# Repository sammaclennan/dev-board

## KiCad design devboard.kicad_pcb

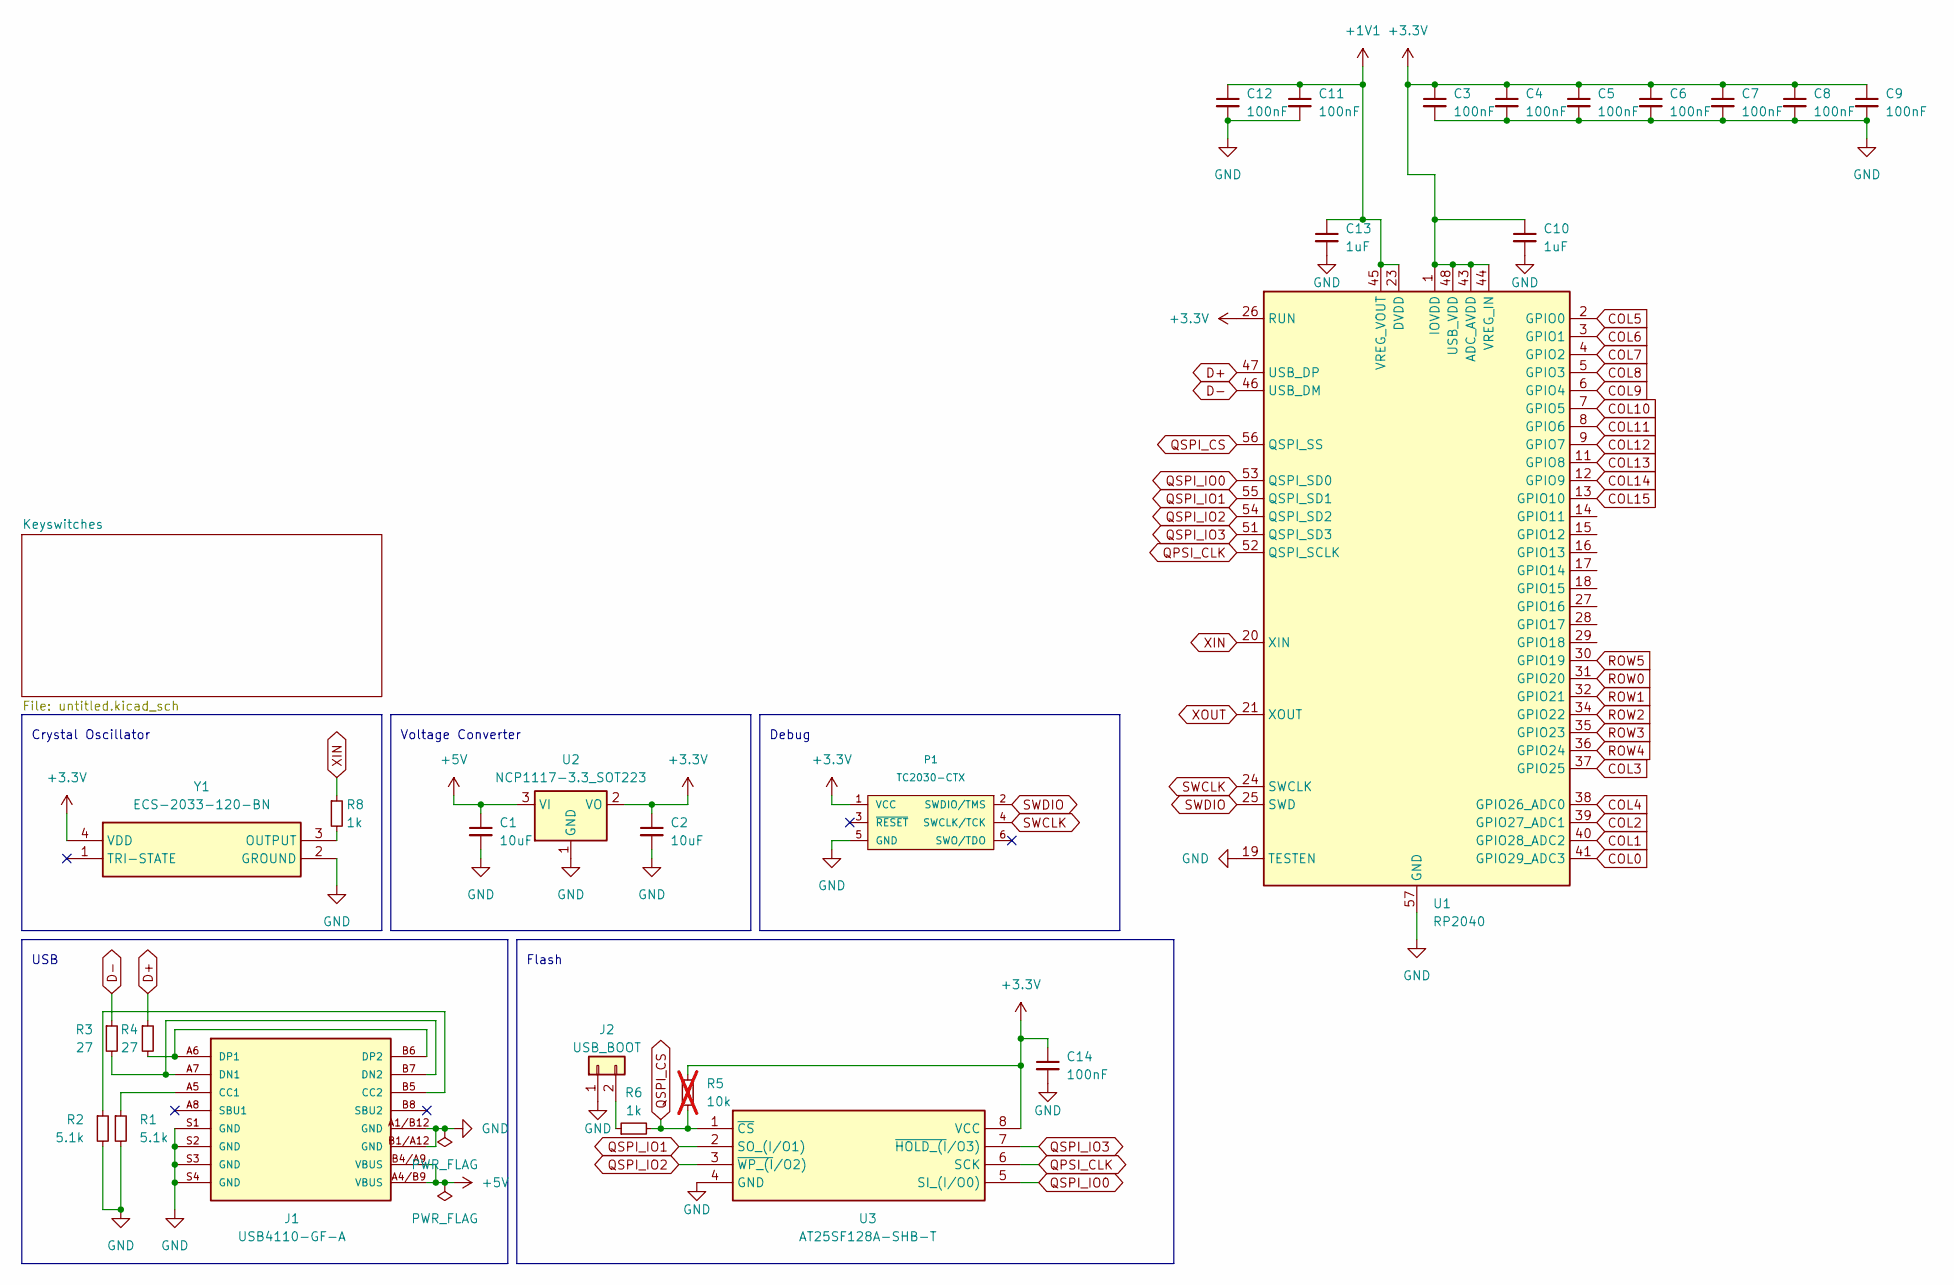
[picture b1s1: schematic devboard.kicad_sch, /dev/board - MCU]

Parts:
C1, C2: 10uF; C_0402_1005Metric
C3, C4, C5, C6, C7, C8, C9, C11, C12, C14: 100nF; C_0402_1005Metric
C10, C13: 1uF; C_0402_1005Metric
J1: USB4110-GF-A; GCT_USB4110GFA
J2: USB_BOOT; PinHeader_1x02_P2.54mm_Vertical
P1: TC2030-CTX; TC2030-IDC-NL
R1, R2: 5.1k; R_0402_1005Metric
R3, R4: 27; R_0402_1005Metric
R5: 10k; R_0402_1005Metric; not fitted
R6, R8: 1k; R_0402_1005Metric
U1: RP2040; QFN-56-1EP_7x7mm_P0.4mm_EP3.2x3.2mm
U2: NCP1117-3.3_SOT223; SOT-223-3_TabPin2
U3: AT25SF128A-SHB-T; Manufacturer_Part_Number AT25SF128A-SHB-T; Mouser Part Number 988-AT25SF128A-SHB-T
Y1: ECS-2033-120-BN; Manufacturer_Part_Number ECS-2033-120-BN; Mouser Part Number 520-2033-120-BN

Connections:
+1V1: C11.1, C12.1, C13.1, U1.23 (DVDD), U1.45 (VREG_VOUT), U1.50 (DVDD)
+3.3V: C2.1, C3.1, C4.1, C5.1, C6.1, C7.1, C8.1, C9.1, C10.1, C14.1, P1.1 (VCC), R5.1, U1.1 (IOVDD), U1.10 (IOVDD), U1.22 (IOVDD), U1.26 (RUN), U1.33 (IOVDD), U1.42 (IOVDD), U1.43 (ADC_AVDD), U1.44 (VREG_IN), U1.48 (USB_VDD), U1.49 (IOVDD), U2.2 (VO), U3.8 (VCC), Y1.4 (VDD)
+5V: C1.1, J1.A4/B9 (VBUS), J1.B4/A9 (VBUS), U2.3 (VI)
COL0: U1.41 (GPIO29_ADC3); also elsewhere on the board
COL1: U1.40 (GPIO28_ADC2); also elsewhere on the board
COL2: U1.39 (GPIO27_ADC1); also elsewhere on the board
COL3: U1.37 (GPIO25); also elsewhere on the board
COL4: U1.38 (GPIO26_ADC0); also elsewhere on the board
COL5: U1.2 (GPIO0); also elsewhere on the board
COL6: U1.3 (GPIO1); also elsewhere on the board
COL7: U1.4 (GPIO2); also elsewhere on the board
COL8: U1.5 (GPIO3); also elsewhere on the board
COL9: U1.6 (GPIO4); also elsewhere on the board
COL10: U1.7 (GPIO5); also elsewhere on the board
COL11: U1.8 (GPIO6); also elsewhere on the board
COL12: U1.9 (GPIO7); also elsewhere on the board
COL13: U1.11 (GPIO8); also elsewhere on the board
COL14: U1.12 (GPIO9); also elsewhere on the board
COL15: U1.13 (GPIO10); also elsewhere on the board
D+: R4.1, U1.47 (USB_DP)
D-: R3.1, U1.46 (USB_DM)
GND: C1.2, C2.2, C3.2, C4.2, C5.2, C6.2, C7.2, C8.2, C9.2, C10.2, C11.2, C12.2, C13.2, C14.2, J1.A1/B12 (GND), J1.B1/A12 (GND), J1.S1 (GND), J1.S2 (GND), J1.S3 (GND), J1.S4 (GND), J2.1, P1.5 (GND), R1.2, R2.2, U1.19 (TESTEN), U1.57 (GND), U2.1 (GND), U3.4 (GND), Y1.2 (GROUND)
unnamed: J1.A5 (CC1), R1.1
unnamed: J1.B5 (CC2), R2.1
unnamed: J1.A7 (DN1), J1.B7 (DN2), R3.2
unnamed: J1.A6 (DP1), J1.B6 (DP2), R4.2
unnamed: J2.2, R6.1
unnamed: R8.2, Y1.3 (OUTPUT)
QPSI_CLK: U1.52 (QSPI_SCLK), U3.6 (SCK)
QSPI_CS: R5.2, R6.2, U1.56 (QSPI_SS), U3.1 (~CS)
QSPI_IO0: U1.53 (QSPI_SD0), U3.5 (SI_(I/O0))
QSPI_IO1: U1.55 (QSPI_SD1), U3.2 (SO_(I/O1))
QSPI_IO2: U1.54 (QSPI_SD2), U3.3 (~WP_(I/O2))
QSPI_IO3: U1.51 (QSPI_SD3), U3.7 (~HOLD_(I/O3))
ROW0: U1.31 (GPIO20); also elsewhere on the board
ROW1: U1.32 (GPIO21); also elsewhere on the board
ROW2: U1.34 (GPIO22); also elsewhere on the board
ROW3: U1.35 (GPIO23); also elsewhere on the board
ROW4: U1.36 (GPIO24); also elsewhere on the board
ROW5: U1.30 (GPIO19); also elsewhere on the board
SWCLK: P1.4 (SWCLK/TCK), U1.24 (SWCLK)
SWDIO: P1.2 (SWDIO/TMS), U1.25 (SWD)
XIN: R8.1, U1.20 (XIN)
XOUT: U1.21 (XOUT)

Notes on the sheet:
Crystal Oscillator
Debug
Voltage Converter
Flash
USB

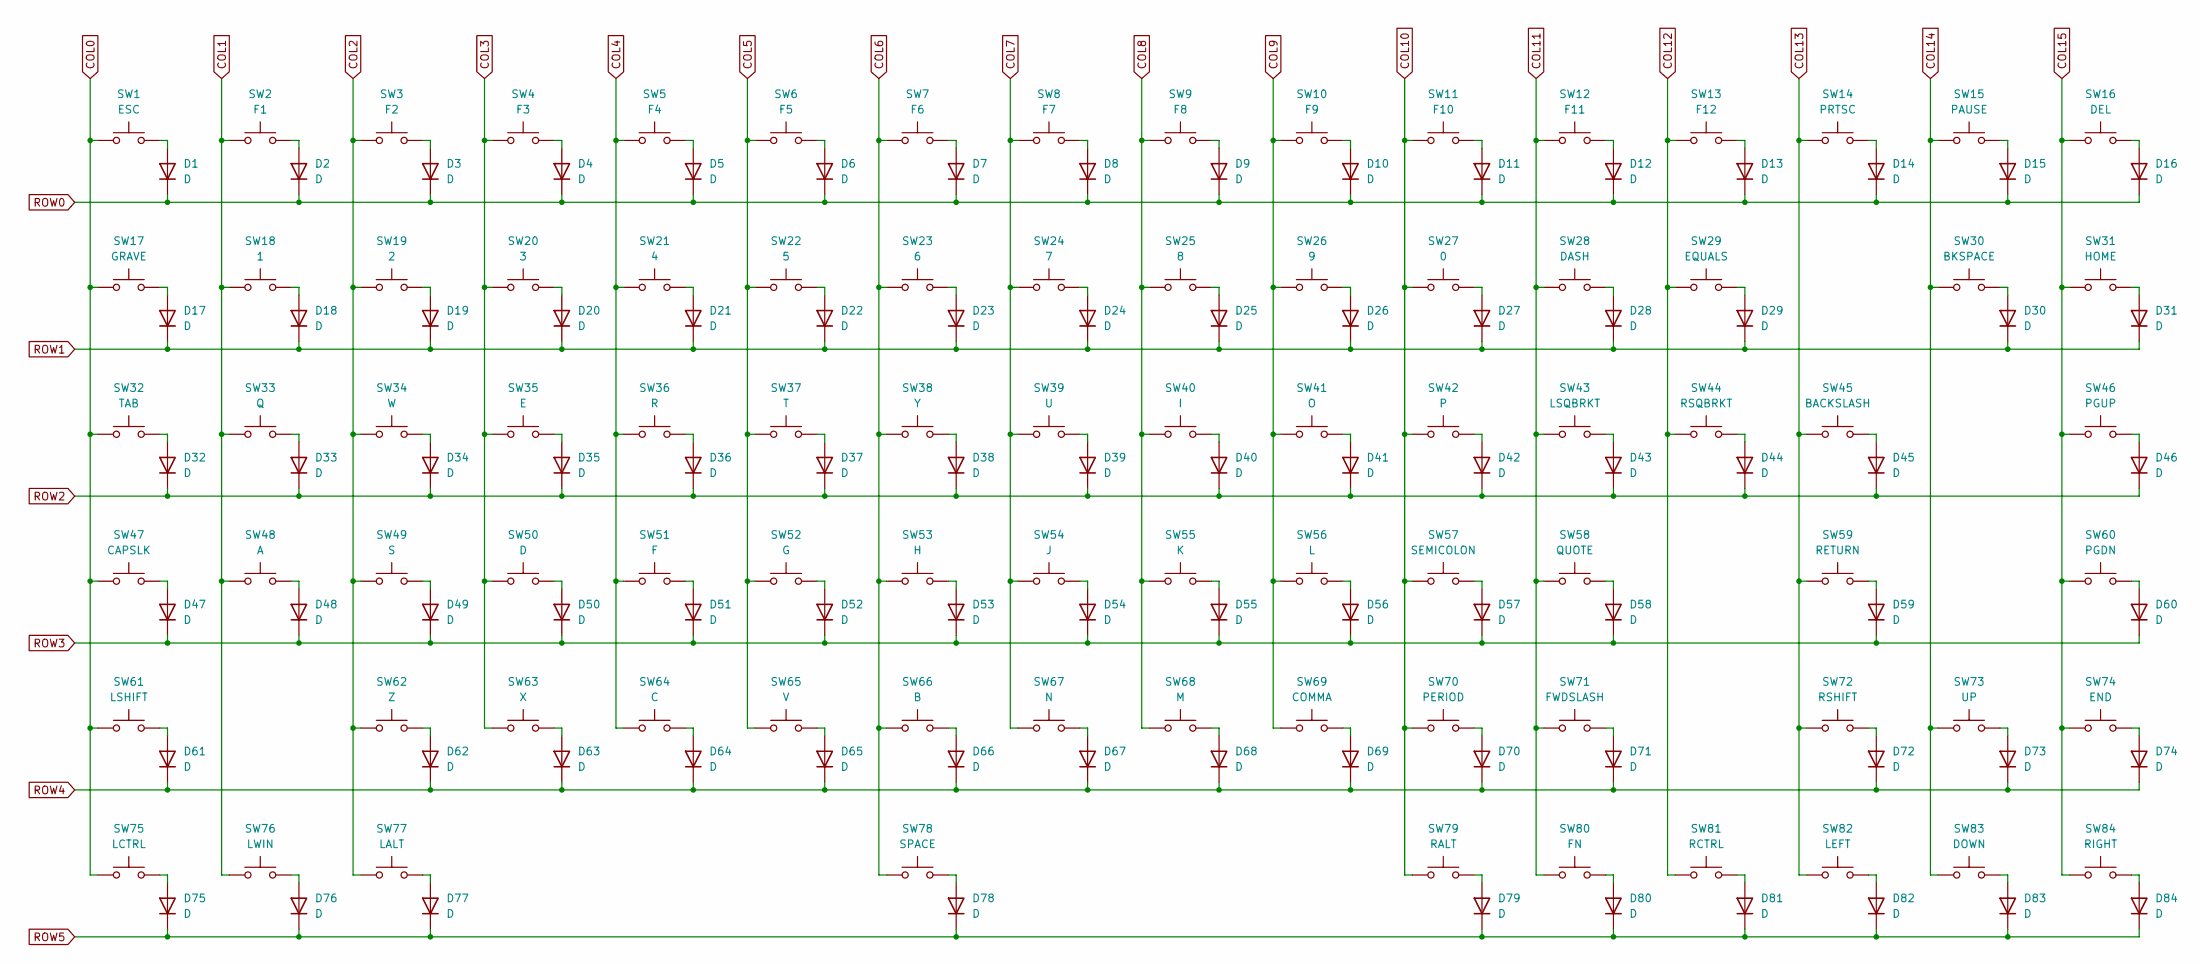
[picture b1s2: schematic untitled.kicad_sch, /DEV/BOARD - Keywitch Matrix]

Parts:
D1, D2, D3, D4, D5, D6, D7, D8, D9, D10, D11, D12, D13, D14, D15, D16, D17, D18, D19, D20, D21, D22, D23, D24, D25, D26, D27, D28, D29, D30, D31, D32, D33, D34, D35, D36, D37, D38, D39, D40, D41, D42, D43, D44, D45, D46, D47, D48, D49, D50, D51, D52, D53, D54, D55, D56, D57, D58, D59, D60, D61, D62, D63, D64, D65, D66, D67, D68, D69, D70, D71, D72, D73, D74, D75, D76, D77, D78, D79, D80, D81, D82, D83, D84: D; D_SOD-323F
SW1: ESC; SW_Cherry_MX_1.00u_PCB
SW2: F1; SW_Cherry_MX_1.00u_PCB
SW3: F2; SW_Cherry_MX_1.00u_PCB
SW4: F3; SW_Cherry_MX_1.00u_PCB
SW5: F4; SW_Cherry_MX_1.00u_PCB
SW6: F5; SW_Cherry_MX_1.00u_PCB
SW7: F6; SW_Cherry_MX_1.00u_PCB
SW8: F7; SW_Cherry_MX_1.00u_PCB
SW9: F8; SW_Cherry_MX_1.00u_PCB
SW10: F9; SW_Cherry_MX_1.00u_PCB
SW11: F10; SW_Cherry_MX_1.00u_PCB
SW12: F11; SW_Cherry_MX_1.00u_PCB
SW13: F12; SW_Cherry_MX_1.00u_PCB
SW14: PRTSC; SW_Cherry_MX_1.00u_PCB
SW15: PAUSE; SW_Cherry_MX_1.00u_PCB
SW16: DEL; SW_Cherry_MX_1.00u_PCB
SW17: GRAVE; SW_Cherry_MX_1.00u_PCB
SW18: 1; SW_Cherry_MX_1.00u_PCB
SW19: 2; SW_Cherry_MX_1.00u_PCB
SW20: 3; SW_Cherry_MX_1.00u_PCB
SW21: 4; SW_Cherry_MX_1.00u_PCB
SW22: 5; SW_Cherry_MX_1.00u_PCB
SW23: 6; SW_Cherry_MX_1.00u_PCB
SW24: 7; SW_Cherry_MX_1.00u_PCB
SW25: 8; SW_Cherry_MX_1.00u_PCB
SW26: 9; SW_Cherry_MX_1.00u_PCB
SW27: 0; SW_Cherry_MX_1.00u_PCB
SW28: DASH; SW_Cherry_MX_1.00u_PCB
SW29: EQUALS; SW_Cherry_MX_1.00u_PCB
SW30: BKSPACE; SW_Cherry_MX_2.00u_PCB
SW31: HOME; SW_Cherry_MX_1.00u_PCB
SW32: TAB; SW_Cherry_MX_1.50u_PCB
SW33: Q; SW_Cherry_MX_1.00u_PCB
SW34: W; SW_Cherry_MX_1.00u_PCB
SW35: E; SW_Cherry_MX_1.00u_PCB
SW36: R; SW_Cherry_MX_1.00u_PCB
SW37: T; SW_Cherry_MX_1.00u_PCB
SW38: Y; SW_Cherry_MX_1.00u_PCB
SW39: U; SW_Cherry_MX_1.00u_PCB
SW40: I; SW_Cherry_MX_1.00u_PCB
SW41: O; SW_Cherry_MX_1.00u_PCB
SW42: P; SW_Cherry_MX_1.00u_PCB
SW43: LSQBRKT; SW_Cherry_MX_1.00u_PCB
SW44: RSQBRKT; SW_Cherry_MX_1.00u_PCB
SW45: BACKSLASH; SW_Cherry_MX_1.50u_PCB
SW46: PGUP; SW_Cherry_MX_1.00u_PCB
SW47: CAPSLK; SW_Cherry_MX_1.75u_PCB
SW48: A; SW_Cherry_MX_1.00u_PCB
SW49: S; SW_Cherry_MX_1.00u_PCB
SW50: D; SW_Cherry_MX_1.00u_PCB
SW51: F; SW_Cherry_MX_1.00u_PCB
SW52: G; SW_Cherry_MX_1.00u_PCB
SW53: H; SW_Cherry_MX_1.00u_PCB
SW54: J; SW_Cherry_MX_1.00u_PCB
SW55: K; SW_Cherry_MX_1.00u_PCB
SW56: L; SW_Cherry_MX_1.00u_PCB
SW57: SEMICOLON; SW_Cherry_MX_1.00u_PCB
SW58: QUOTE; SW_Cherry_MX_1.00u_PCB
SW59: RETURN; SW_Cherry_MX_2.25u_PCB
SW60: PGDN; SW_Cherry_MX_1.00u_PCB
SW61: LSHIFT; SW_Cherry_MX_2.25u_PCB
SW62: Z; SW_Cherry_MX_1.00u_PCB
SW63: X; SW_Cherry_MX_1.00u_PCB
SW64: C; SW_Cherry_MX_1.00u_PCB
SW65: V; SW_Cherry_MX_1.00u_PCB
SW66: B; SW_Cherry_MX_1.00u_PCB
SW67: N; SW_Cherry_MX_1.00u_PCB
SW68: M; SW_Cherry_MX_1.00u_PCB
SW69: COMMA; SW_Cherry_MX_1.00u_PCB
SW70: PERIOD; SW_Cherry_MX_1.00u_PCB
SW71: FWDSLASH; SW_Cherry_MX_1.00u_PCB
SW72: RSHIFT; SW_Cherry_MX_1.75u_PCB
SW73: UP; SW_Cherry_MX_1.00u_PCB
SW74: END; SW_Cherry_MX_1.00u_PCB
SW75: LCTRL; SW_Cherry_MX_1.25u_PCB
SW76: LWIN; SW_Cherry_MX_1.25u_PCB
SW77: LALT; SW_Cherry_MX_1.25u_PCB
SW78: SPACE; SW_Cherry_MX_6.25u_PCB
SW79: RALT; SW_Cherry_MX_1.00u_PCB
SW80: FN; SW_Cherry_MX_1.00u_PCB
SW81: RCTRL; SW_Cherry_MX_1.00u_PCB
SW82: LEFT; SW_Cherry_MX_1.00u_PCB
SW83: DOWN; SW_Cherry_MX_1.00u_PCB
SW84: RIGHT; SW_Cherry_MX_1.00u_PCB

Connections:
COL0: SW1.1, SW17.1, SW32.1, SW47.1, SW61.1, SW75.1; also elsewhere on the board
COL1: SW2.1, SW18.1, SW33.1, SW48.1, SW76.1; also elsewhere on the board
COL2: SW3.1, SW19.1, SW34.1, SW49.1, SW62.1, SW77.1; also elsewhere on the board
COL3: SW4.1, SW20.1, SW35.1, SW50.1, SW63.1; also elsewhere on the board
COL4: SW5.1, SW21.1, SW36.1, SW51.1, SW64.1; also elsewhere on the board
COL5: SW6.1, SW22.1, SW37.1, SW52.1, SW65.1; also elsewhere on the board
COL6: SW7.1, SW23.1, SW38.1, SW53.1, SW66.1, SW78.1; also elsewhere on the board
COL7: SW8.1, SW24.1, SW39.1, SW54.1, SW67.1; also elsewhere on the board
COL8: SW9.1, SW25.1, SW40.1, SW55.1, SW68.1; also elsewhere on the board
COL9: SW10.1, SW26.1, SW41.1, SW56.1, SW69.1; also elsewhere on the board
COL10: SW11.1, SW27.1, SW42.1, SW57.1, SW70.1, SW79.1; also elsewhere on the board
COL11: SW12.1, SW28.1, SW43.1, SW58.1, SW71.1, SW80.1; also elsewhere on the board
COL12: SW13.1, SW29.1, SW44.1, SW81.1; also elsewhere on the board
COL13: SW14.1, SW45.1, SW59.1, SW72.1, SW82.1; also elsewhere on the board
COL14: SW15.1, SW30.1, SW73.1, SW83.1; also elsewhere on the board
COL15: SW16.1, SW31.1, SW46.1, SW60.1, SW74.1, SW84.1; also elsewhere on the board
unnamed: D1.2 (A), SW1.2
unnamed: D2.2 (A), SW2.2
unnamed: D3.2 (A), SW3.2
unnamed: D4.2 (A), SW4.2
unnamed: D5.2 (A), SW5.2
unnamed: D6.2 (A), SW6.2
unnamed: D7.2 (A), SW7.2
unnamed: D8.2 (A), SW8.2
unnamed: D9.2 (A), SW9.2
unnamed: D10.2 (A), SW10.2
unnamed: D11.2 (A), SW11.2
unnamed: D12.2 (A), SW12.2
unnamed: D13.2 (A), SW13.2
unnamed: D14.2 (A), SW14.2
unnamed: D15.2 (A), SW15.2
unnamed: D16.2 (A), SW16.2
unnamed: D17.2 (A), SW17.2
unnamed: D18.2 (A), SW18.2
unnamed: D19.2 (A), SW19.2
unnamed: D20.2 (A), SW20.2
unnamed: D21.2 (A), SW21.2
unnamed: D22.2 (A), SW22.2
unnamed: D23.2 (A), SW23.2
unnamed: D24.2 (A), SW24.2
unnamed: D25.2 (A), SW25.2
unnamed: D26.2 (A), SW26.2
unnamed: D27.2 (A), SW27.2
unnamed: D28.2 (A), SW28.2
unnamed: D29.2 (A), SW29.2
unnamed: D30.2 (A), SW30.2
unnamed: D31.2 (A), SW31.2
unnamed: D32.2 (A), SW32.2
unnamed: D33.2 (A), SW33.2
unnamed: D34.2 (A), SW34.2
unnamed: D35.2 (A), SW35.2
unnamed: D36.2 (A), SW36.2
unnamed: D37.2 (A), SW37.2
unnamed: D38.2 (A), SW38.2
unnamed: D39.2 (A), SW39.2
unnamed: D40.2 (A), SW40.2
unnamed: D41.2 (A), SW41.2
unnamed: D42.2 (A), SW42.2
unnamed: D43.2 (A), SW43.2
unnamed: D44.2 (A), SW44.2
unnamed: D45.2 (A), SW45.2
unnamed: D46.2 (A), SW46.2
unnamed: D47.2 (A), SW47.2
unnamed: D48.2 (A), SW48.2
unnamed: D49.2 (A), SW49.2
unnamed: D50.2 (A), SW50.2
unnamed: D51.2 (A), SW51.2
unnamed: D52.2 (A), SW52.2
unnamed: D53.2 (A), SW53.2
unnamed: D54.2 (A), SW54.2
unnamed: D55.2 (A), SW55.2
unnamed: D56.2 (A), SW56.2
unnamed: D57.2 (A), SW57.2
unnamed: D58.2 (A), SW58.2
unnamed: D59.2 (A), SW59.2
unnamed: D60.2 (A), SW60.2
unnamed: D61.2 (A), SW61.2
unnamed: D62.2 (A), SW62.2
unnamed: D63.2 (A), SW63.2
unnamed: D64.2 (A), SW64.2
unnamed: D65.2 (A), SW65.2
unnamed: D66.2 (A), SW66.2
unnamed: D67.2 (A), SW67.2
unnamed: D68.2 (A), SW68.2
unnamed: D69.2 (A), SW69.2
unnamed: D70.2 (A), SW70.2
unnamed: D71.2 (A), SW71.2
unnamed: D72.2 (A), SW72.2
unnamed: D73.2 (A), SW73.2
unnamed: D74.2 (A), SW74.2
unnamed: D75.2 (A), SW75.2
unnamed: D76.2 (A), SW76.2
unnamed: D77.2 (A), SW77.2
unnamed: D78.2 (A), SW78.2
unnamed: D79.2 (A), SW79.2
unnamed: D80.2 (A), SW80.2
unnamed: D81.2 (A), SW81.2
unnamed: D82.2 (A), SW82.2
unnamed: D83.2 (A), SW83.2
unnamed: D84.2 (A), SW84.2
ROW0: D1.1 (K), D2.1 (K), D3.1 (K), D4.1 (K), D5.1 (K), D6.1 (K), D7.1 (K), D8.1 (K), D9.1 (K), D10.1 (K), D11.1 (K), D12.1 (K), D13.1 (K), D14.1 (K), D15.1 (K), D16.1 (K); also elsewhere on the board
ROW1: D17.1 (K), D18.1 (K), D19.1 (K), D20.1 (K), D21.1 (K), D22.1 (K), D23.1 (K), D24.1 (K), D25.1 (K), D26.1 (K), D27.1 (K), D28.1 (K), D29.1 (K), D30.1 (K), D31.1 (K); also elsewhere on the board
ROW2: D32.1 (K), D33.1 (K), D34.1 (K), D35.1 (K), D36.1 (K), D37.1 (K), D38.1 (K), D39.1 (K), D40.1 (K), D41.1 (K), D42.1 (K), D43.1 (K), D44.1 (K), D45.1 (K), D46.1 (K); also elsewhere on the board
ROW3: D47.1 (K), D48.1 (K), D49.1 (K), D50.1 (K), D51.1 (K), D52.1 (K), D53.1 (K), D54.1 (K), D55.1 (K), D56.1 (K), D57.1 (K), D58.1 (K), D59.1 (K), D60.1 (K); also elsewhere on the board
ROW4: D61.1 (K), D62.1 (K), D63.1 (K), D64.1 (K), D65.1 (K), D66.1 (K), D67.1 (K), D68.1 (K), D69.1 (K), D70.1 (K), D71.1 (K), D72.1 (K), D73.1 (K), D74.1 (K); also elsewhere on the board
ROW5: D75.1 (K), D76.1 (K), D77.1 (K), D78.1 (K), D79.1 (K), D80.1 (K), D81.1 (K), D82.1 (K), D83.1 (K), D84.1 (K); also elsewhere on the board

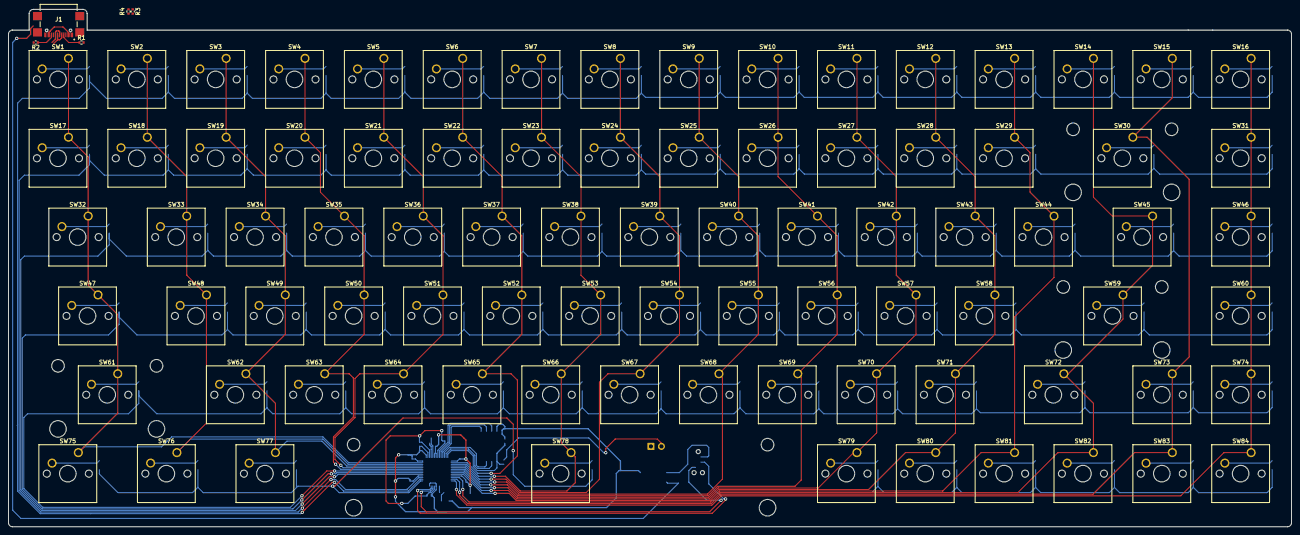
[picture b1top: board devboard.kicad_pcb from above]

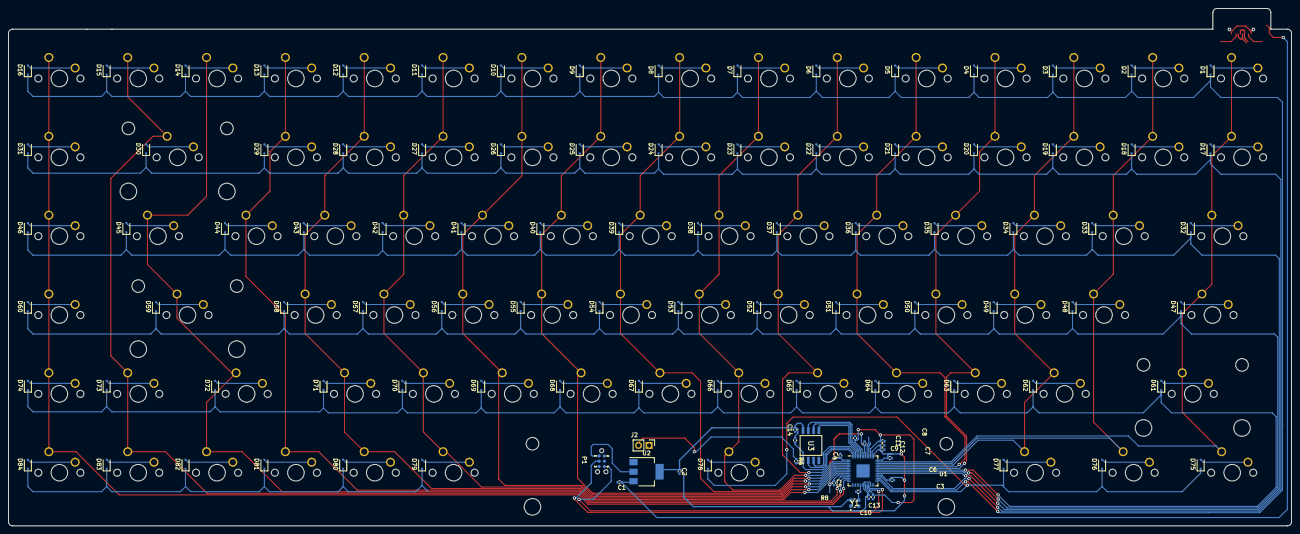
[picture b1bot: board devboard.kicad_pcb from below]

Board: 2 copper layers, 310.0 x 125.0 mm, 196 parts (107 on the bottom side), 127 nets.

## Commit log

2023-01-29 Start RP2040 and ancilliary layout
2023-01-30 Mostly finished rp2040 - ready to do switches
2023-02-01 Key matrix
2023-02-02 Key matrix actually done - probably need a debug plan
2023-04-05 Update some meta project stuff
2023-04-06 Clean up some DRC things, label the matrix
2023-04-06 Placed switches and diodes
2023-04-27 Full re-route of controller components
2024-02-07 Just redo it all jesus christ
2024-02-11 USB routing and power
2024-02-12 finished??
2024-02-20 Change board size
2025-01-02 Change LDO to DCDC Buck Converter
2025-01-02 Redo some routing and placement
2025-01-03 Redid power planes and USB routing
2025-01-03 Change 5v routing a little
2025-01-10 Changes to make JLC happy
2025-01-16 CAD Changes
